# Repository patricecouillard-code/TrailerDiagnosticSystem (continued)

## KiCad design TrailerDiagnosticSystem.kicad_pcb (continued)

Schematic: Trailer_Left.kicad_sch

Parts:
D1601: MUR1520G; TO-220-2_Vertical
D1602: P6KE39A; D_DO-15_P10.16mm_Horizontal_Zener
DZ1601: 1N5242B; D_DO-35_SOD27_P7.62mm_Horizontal_Zener
F1601: MF-R700; PTC_Bourns_MF-R_P10.20mm_W24.2mm
Q1601: 2N7000; TO-92_Inline_Wide_SGD
Q1602: IRF4905PBF; TO-220-3_Vertical
Q1603: 2N3906; TO-92_Inline_Wide_EBC
R1601, R1603, R1605, R1607: 10kΩ; R_Axial_DIN0207_L6.3mm_D2.5mm_P10.16mm_Horizontal
R1602, R1606: 1kΩ; R_Axial_DIN0207_L6.3mm_D2.5mm_P10.16mm_Horizontal
R1604: 2.7kΩ; R_Axial_DIN0207_L6.3mm_D2.5mm_P10.16mm_Horizontal
R1608: 39kΩ; R_Axial_DIN0207_L6.3mm_D2.5mm_P10.16mm_Horizontal
R1609: 12Ω 2W; R_Axial_DIN0414_L11.9mm_D4.5mm_P15.24mm_Horizontal; MPN PR02000201209JR500
R1610, R1611: 10kΩ; TRIM_3296W1103LF; MPN 3296W-1-103LF
R1612, R1613: 4.7kΩ; R_Axial_DIN0207_L6.3mm_D2.5mm_P10.16mm_Horizontal
SW1601: 82-4153.2000
U1601: LM2901N; DIP-14_W7.62mm_Socket

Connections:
/Canal_Left/Bloc_Test_Left/Trailer_Court_Left: R1613.1, U1601.13; also elsewhere on the board
/Canal_Left/Bloc_Test_Left/Trailer_Ouvert_Left: R1612.1, U1601.1; also elsewhere on the board
/Canal_Left/Trailer_Left/Court_Sense: R1605.1, R1608.1, U1601.10 (-)
/Canal_Left/Trailer_Left/I_Present: R1604.1, R1607.2, U1601.6 (-)
/Trailer_Fil_Left: D1601.1 (K), D1602.1 (K), R1606.1, R1608.2, R1609.2; also elsewhere on the board
Facade_Btn_Left: Q1601.2 (G), R1601.2, SW1601.2 (B); also elsewhere on the board
GND: D1602.2 (A), Q1601.1 (S), R1601.1, R1604.2, R1605.2, R1610.3, R1611.1, SW1601.3 (C), U1601.5 (+), U1601.9 (+), U1601.12 (V-); also elsewhere on the board
unnamed: D1601.2 (A), Q1602.2 (D), Q1603.1 (E), R1609.1
unnamed: DZ1601.2 (A), Q1602.1 (G), R1602.2, R1603.1
unnamed: DZ1601.1 (K), F1601.2, Q1602.3 (S), R1603.2
unnamed: Q1601.3 (D), R1602.1
unnamed: Q1603.2 (B), R1606.2
unnamed: Q1603.3 (C), R1607.1
unnamed: R1610.2, U1601.7 (+)
unnamed: R1611.2, U1601.11 (+)
Trailer_V_Arm: F1601.1; also elsewhere on the board
V_Ref: R1610.1, R1611.3, R1612.2, R1613.2, SW1601.1 (A), U1601.3 (V+), U1601.4 (-), U1601.8 (-); also elsewhere on the board

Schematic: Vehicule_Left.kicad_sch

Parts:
OC1501, OC1502: PC817; DIP-4_W7.62mm_LongPads
Q1501: IRLZ44N; TO-220-3_Vertical_GDS
R1501: 12Ω 25W; TerminalBlock_Phoenix_PT-1,5-2-3.5-H_1x02_P3.50mm_Horizontal; MPN HSA2512RJ
R1502: 0.2Ω 5W; R_Axial_Power_L25.0mm_W9.0mm_P27.94mm; MPN SQP500JB-0R2
R1503, R1504, R1505: 4.7kΩ; R_Axial_DIN0207_L6.3mm_D2.5mm_P10.16mm_Horizontal
R1506, R1507: 1kΩ; R_Axial_DIN0207_L6.3mm_D2.5mm_P10.16mm_Horizontal
R1508: 100kΩ; R_Axial_DIN0207_L6.3mm_D2.5mm_P10.16mm_Horizontal
R1509: 10kΩ; R_Axial_DIN0207_L6.3mm_D2.5mm_P10.16mm_Horizontal
R1510, R1511, R1512: 10kΩ; TRIM_3296W1103LF; MPN 3296W-1-103LF
U1501: LM2901N; DIP-14_W7.62mm_Socket

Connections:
/Canal_Left/Bloc_Test_Left/Vehic_Court_Left: OC1501.4; also elsewhere on the board
/Canal_Left/Bloc_Test_Left/Vehic_Ouvert_Left: OC1502.4; also elsewhere on the board
/Canal_Left/Vehicule_Left/Injection_Drain: Q1501.2 (D), R1501.2
/Canal_Left/Vehicule_Left/Injection_Fault: Q1501.1 (G), R1503.1, U1501.2
/Canal_Left/Vehicule_Left/Opto_Court: OC1501.2, R1505.1, U1501.13
/Canal_Left/Vehicule_Left/Opto_Ouvert: OC1502.2, R1504.1, U1501.1
/Canal_Left/Vehicule_Left/Seuil_Court: R1512.2, U1501.10 (-)
/Canal_Left/Vehicule_Left/Seuil_Injection: R1510.2, U1501.4 (-)
/Canal_Left/Vehicule_Left/Seuil_Ouvert: R1511.2, U1501.7 (+)
/Canal_Left/Vehicule_Left/Vehic_Shunt_Haut: Q1501.3 (S), R1502.1, U1501.6 (-), U1501.11 (+)
/Vehic_Fil_Left: R1501.1, R1508.1; also elsewhere on the board
GND: OC1501.3, OC1502.3, R1502.2, R1509.2, R1510.3, R1511.3, R1512.3, U1501.9 (+), U1501.12 (V-); also elsewhere on the board
unnamed: OC1501.1, R1506.2
unnamed: OC1502.1, R1507.2
unnamed: R1508.2, R1509.1, U1501.5 (+)
V_Ref: R1503.2, R1504.2, R1505.2, R1506.1, R1507.1, R1510.1, R1511.1, R1512.1, U1501.3 (V+), U1501.8 (-); also elsewhere on the board

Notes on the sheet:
Injection
Ouvvert
Non_Utilisé
Court-circuit

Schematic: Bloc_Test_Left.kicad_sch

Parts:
D1701, D1702, D1703, D1704, D1705, D1706, D1707, D1708, D1709, D1710, D1711, D1712, D1713, D1714, D1715, D1716, D1717, D1718, D1719, D1720, D1721, D1722, D1723: 1N4148; D_DO-35_SOD27_P7.62mm_Horizontal
D1724: RGB 5mm CA; LED_D5.0mm-4_RGB_Staggered_Pins; MPN WP154A4SEJ3VBDZGW/CA
Q1701, Q1702, Q1703, Q1704, Q1705, Q1706: 2N7000; TO-92_Inline_Wide_SGD
R1701, R1704, R1707, R1708, R1710, R1711, R1715: 4.7kΩ; R_Axial_DIN0207_L6.3mm_D2.5mm_P10.16mm_Horizontal
R1702, R1705, R1709: 470kΩ; R_Axial_DIN0207_L6.3mm_D2.5mm_P10.16mm_Horizontal
R1703, R1706: 100kΩ; R_Axial_DIN0207_L6.3mm_D2.5mm_P10.16mm_Horizontal
R1712: 680Ω; R_Axial_DIN0207_L6.3mm_D2.5mm_P10.16mm_Horizontal
R1713: 470Ω; R_Axial_DIN0207_L6.3mm_D2.5mm_P10.16mm_Horizontal
R1714: 150Ω; R_Axial_DIN0207_L6.3mm_D2.5mm_P10.16mm_Horizontal

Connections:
/Canal_Left/Bloc_Test_Left/Bleu: D1704.2 (A), D1713.2 (A), D1722.2 (A), D1723.2 (A), R1715.1
/Canal_Left/Bloc_Test_Left/Court: D1709.1 (K), D1710.1 (K), D1711.2 (A), D1717.2 (A), Q1701.2 (G), R1706.2
/Canal_Left/Bloc_Test_Left/Fault_Actif: D1711.1 (K), D1712.1 (K), D1713.1 (K), Q1702.2 (G), R1705.1
/Canal_Left/Bloc_Test_Left/Not_Btn: D1723.1 (K), Q1703.3 (D), R1711.2
/Canal_Left/Bloc_Test_Left/Ouvert: D1703.2 (A), D1705.1 (K), D1706.1 (K), D1712.2 (A), D1718.2 (A), R1703.2
/Canal_Left/Bloc_Test_Left/Ouvert_Ou_Bleu: D1703.1 (K), D1704.1 (K), Q1701.3 (D), Q1706.2 (G), R1702.2
/Canal_Left/Bloc_Test_Left/Rouge_Enable: D1717.1 (K), D1718.1 (K), Q1704.2 (G), R1709.2
/Canal_Left/Bloc_Test_Left/Trailer_Court_Actif: D1707.2 (A), D1708.2 (A), D1710.2 (A), D1716.2 (A), R1704.1
/Canal_Left/Bloc_Test_Left/Trailer_Court_Left: D1707.1 (K); also elsewhere on the board
/Canal_Left/Bloc_Test_Left/Trailer_Ouvert_Actif: D1706.2 (A), D1719.2 (A), D1720.2 (A), D1721.2 (A), R1710.1
/Canal_Left/Bloc_Test_Left/Trailer_Ouvert_Left: D1719.1 (K); also elsewhere on the board
/Canal_Left/Bloc_Test_Left/Vehic_Court_Actif: D1701.2 (A), D1702.2 (A), D1709.2 (A), R1701.1
/Canal_Left/Bloc_Test_Left/Vehic_Court_Left: D1701.1 (K); also elsewhere on the board
/Canal_Left/Bloc_Test_Left/Vehic_Ouvert_Actif: D1705.2 (A), D1714.2 (A), D1715.2 (A), R1708.1
/Canal_Left/Bloc_Test_Left/Vehic_Ouvert_Left: D1714.1 (K); also elsewhere on the board
/Canal_Left/Bloc_Test_Left/Vert_Enable: Q1702.3 (D), Q1705.2 (G), R1707.2
Facade_Btn_Left: D1716.1 (K), D1721.1 (K), Q1703.2 (G); also elsewhere on the board
Facade_Left_B: D1724.3 (BK), R1714.2; also elsewhere on the board
Facade_Left_G: D1724.4 (GK), R1713.2; also elsewhere on the board
Facade_Left_R: D1724.1 (RK), R1712.2; also elsewhere on the board
GND: Q1701.1 (S), Q1702.1 (S), Q1703.1 (S), Q1704.1 (S), Q1705.1 (S), Q1706.1 (S), R1702.1, R1703.1, R1705.2, R1706.1, R1709.1; also elsewhere on the board
Mode_Trailer: D1708.1 (K), D1720.1 (K), D1722.1 (K); also elsewhere on the board
Mode_Vehic: D1702.1 (K), D1715.1 (K); also elsewhere on the board
unnamed: Q1704.3 (D), R1712.1
unnamed: Q1705.3 (D), R1713.1
unnamed: Q1706.3 (D), R1714.1
V_Ref: D1724.2 (A), R1701.2, R1704.2, R1707.1, R1708.2, R1710.2, R1711.1, R1715.2; also elsewhere on the board

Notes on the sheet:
====================================== NIVEAU 3 ==================
3ième Porte "ET" (Ouvert_V_Actif_Left)
Porte OU Fault_Actif_Left (3 entrées) + inverseur vert
5ième Porte "ET" (Bleu_Left)
Porte OU Rouge_Enable_Left
Porte OU Ouvert_Ou_Bleu_Left + override
2ième Porte "ET" (Court_T_Actif_Left)
========================================================================== NIVEAU 1 ==========================================================================
Inverseur (Dépendance de Bleu_Left)
=========================================== NIVEAU 2 =================================================
1ère Porte "ET" (Court_V_Actif_Left)
2ième Porte "OU" (Court_Left)
4ième Porte "ET" (Ouvert_T_Actif_Left)
1ère Porte "OU" (Ouvert_Left)

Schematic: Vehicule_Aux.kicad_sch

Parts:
C2701: 4.7µF 63V; C_Rect_L19.0mm_W7.0mm_P15.00mm_MKS4; MPN MKS4C044704D00KSSD 10%
D2701: RGB 5mm CA (ambre); LED_D5.0mm-4_RGB_Staggered_Pins; MPN WP154A4SEJ3VBDZGW/CA
OC2701, OC2702: PC817; DIP-4_W7.62mm_LongPads
Q2701: IRLZ44N; TO-220-3_Vertical_GDS
Q2702, Q2703: 2N7000; TO-92_Inline_Wide_SGD
R2701: 0.05Ω 5W; R_Axial_Power_L25.0mm_W9.0mm_P27.94mm; MPN 15FR050E
R2702, R2716: 100kΩ; R_Axial_DIN0207_L6.3mm_D2.5mm_P10.16mm_Horizontal
R2703, R2704, R2705: 10kΩ; R_Axial_DIN0207_L6.3mm_D2.5mm_P10.16mm_Horizontal
R2706, R2708: 4.7kΩ; R_Axial_DIN0207_L6.3mm_D2.5mm_P10.16mm_Horizontal
R2707: 330kΩ; R_Axial_DIN0207_L6.3mm_D2.5mm_P10.16mm_Horizontal
R2709: 4.7Ω 50W; TerminalBlock_Phoenix_PT-1,5-2-3.5-H_1x02_P3.50mm_Horizontal; MPN HSA504R7J
R2710, R2711: 1kΩ; R_Axial_DIN0207_L6.3mm_D2.5mm_P10.16mm_Horizontal
R2712, R2713, R2714: 10kΩ; TRIM_3296W1103LF; MPN 3296W-1-103LF
R2715: 100Ω; R_Axial_DIN0207_L6.3mm_D2.5mm_P10.16mm_Horizontal
TH2701: Thermostat 95°C NC; TerminalBlock_Phoenix_PT-1,5-2-3.5-H_1x02_P3.50mm_Horizontal; MPN CS709525Y
U2701: LM2901N; DIP-14_W7.62mm_Socket

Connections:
/Canal_Aux/Bloc_Test_Aux/Vehic_Court_Aux: OC2702.4; also elsewhere on the board
/Canal_Aux/Bloc_Test_Aux/Vehic_Ouvert_Aux: OC2701.4; also elsewhere on the board
/Canal_Aux/Vehicule_Aux/Etire: C2701.1, R2707.1, U2701.1, U2701.9 (+)
/Canal_Aux/Vehicule_Aux/Injection_Fault: Q2701.1 (G), Q2703.3 (D), R2706.1, U2701.2
/Canal_Aux/Vehicule_Aux/Opto_Ouvert: OC2701.2, U2701.14
/Canal_Aux/Vehicule_Aux/Seuil_Court: R2714.2, U2701.10 (-)
/Canal_Aux/Vehicule_Aux/Seuil_Injection: R2712.2, U2701.4 (-)
/Canal_Aux/Vehicule_Aux/Seuil_Ouvert: R2713.2, U2701.7 (+)
/Vehic_Fil_Aux: R2702.1, R2709.1; also elsewhere on the board
Facade_DEL_Surchauffe_Aux: D2701.1 (K), R2715.2; also elsewhere on the board
GND: C2701.2, OC2701.3, OC2702.3, Q2702.1 (S), Q2703.1 (S), R2701.2, R2704.2, R2705.2, R2712.3, R2713.3, R2714.3, TH2701.2, U2701.12 (V-); also elsewhere on the board
unnamed: OC2701.1, R2710.2
unnamed: OC2702.1, R2711.2
unnamed: OC2702.2, R2708.1, U2701.13
unnamed: Q2701.2 (D), R2709.2
unnamed: Q2701.3 (S), R2701.1, U2701.6 (-), U2701.11 (+)
unnamed: Q2702.3 (D), R2715.1
unnamed: Q2702.2 (G), Q2703.2 (G), R2716.2, TH2701.1
unnamed: R2702.2, R2704.1, U2701.5 (+)
unnamed: R2703.2, R2705.1, U2701.8 (-)
V_Ref: D2701.2 (A), R2703.1, R2706.2, R2707.2, R2708.2, R2710.1, R2711.1, R2712.1, R2713.1, R2714.1, R2716.1, U2701.3 (V+); also elsewhere on the board

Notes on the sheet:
Protection contre surchauffe
Module du voltmetre/ampèremetre

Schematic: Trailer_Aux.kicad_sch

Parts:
D2801: P6KE39A; D_DO-15_P10.16mm_Horizontal_Zener
DZ2801: 1N5242B; D_DO-35_SOD27_P7.62mm_Horizontal_Zener
F2801: MF-R160; PTC_Bourns_MF-R_P5.10mm_W12.0mm
Q2801: 2N7000; TO-92_Inline_Wide_SGD
Q2802: IRF4905PBF; TO-220-3_Vertical
R2801, R2803, R2806: 10kΩ; R_Axial_DIN0207_L6.3mm_D2.5mm_P10.16mm_Horizontal
R2802: 1kΩ; R_Axial_DIN0207_L6.3mm_D2.5mm_P10.16mm_Horizontal
R2804: 12Ω 50W; TerminalBlock_Phoenix_PT-1,5-2-3.5-H_1x02_P3.50mm_Horizontal; MPN HSA5012RJ
R2805: 39kΩ; R_Axial_DIN0207_L6.3mm_D2.5mm_P10.16mm_Horizontal
R2807, R2808: 10kΩ; TRIM_3296W1103LF; MPN 3296W-1-103LF
R2809: 100kΩ; R_Axial_DIN0207_L6.3mm_D2.5mm_P10.16mm_Horizontal
R2810, R2811: 4.7kΩ; R_Axial_DIN0207_L6.3mm_D2.5mm_P10.16mm_Horizontal
SW2801: 82-4153.2000
TH2801: Thermostat 95°C NC; TerminalBlock_Phoenix_PT-1,5-2-3.5-H_1x02_P3.50mm_Horizontal; MPN CS709525Y
U2801: LM2901N; DIP-14_W7.62mm_Socket

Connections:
/Canal_Aux/Bloc_Test_Aux/Trailer_Court_Aux: R2811.1, U2801.13; also elsewhere on the board
/Canal_Aux/Bloc_Test_Aux/Trailer_Ouvert_Aux: R2810.1, U2801.1; also elsewhere on the board
/Canal_Aux/Trailer_Aux/Trailer_Mesure: R2805.2, R2806.2, U2801.7 (+), U2801.10 (-)
/Trailer_Fil_Aux: D2801.1 (K), R2804.1, R2805.1; also elsewhere on the board
Facade_Btn_Aux: Q2801.2 (G), R2801.1, SW2801.2 (B); also elsewhere on the board
GND: D2801.2 (A), Q2801.1 (S), R2801.2, R2806.1, R2807.3, R2808.3, SW2801.3 (C), U2801.5 (+), U2801.9 (+), U2801.12 (V-); also elsewhere on the board
unnamed: DZ2801.2 (A), Q2802.1 (G), R2802.1, R2803.1
unnamed: DZ2801.1 (K), F2801.2, Q2802.3 (S), R2803.2
unnamed: Q2801.3 (D), R2802.2
unnamed: Q2802.2 (D), TH2801.1
unnamed: R2804.2, TH2801.2
unnamed: R2808.1, R2809.1
unnamed: R2807.2, U2801.6 (-)
unnamed: R2808.2, U2801.11 (+)
Trailer_V_Arm: F2801.1; also elsewhere on the board
V_Ref: R2807.1, R2809.2, R2810.2, R2811.2, SW2801.1 (A), U2801.3 (V+), U2801.4 (-), U2801.8 (-); also elsewhere on the board

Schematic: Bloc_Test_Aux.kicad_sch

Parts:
D2901, D2902, D2903, D2904, D2905, D2906, D2907, D2908, D2909, D2910, D2911, D2912, D2913, D2914, D2915, D2916, D2917, D2918, D2919, D2920, D2921, D2922, D2923: 1N4148; D_DO-35_SOD27_P7.62mm_Horizontal
D2924: RGB 5mm CA; LED_D5.0mm-4_RGB_Staggered_Pins; MPN WP154A4SEJ3VBDZGW/CA
Q2901, Q2902, Q2903, Q2904, Q2905, Q2906: 2N7000; TO-92_Inline_Wide_SGD
R2901, R2904, R2907, R2908, R2910, R2911, R2912: 4.7kΩ; R_Axial_DIN0207_L6.3mm_D2.5mm_P10.16mm_Horizontal
R2902, R2905, R2909: 470kΩ; R_Axial_DIN0207_L6.3mm_D2.5mm_P10.16mm_Horizontal
R2903, R2906: 100kΩ; R_Axial_DIN0207_L6.3mm_D2.5mm_P10.16mm_Horizontal
R2913: 680Ω; R_Axial_DIN0207_L6.3mm_D2.5mm_P10.16mm_Horizontal
R2914: 470Ω; R_Axial_DIN0207_L6.3mm_D2.5mm_P10.16mm_Horizontal
R2915: 150Ω; R_Axial_DIN0207_L6.3mm_D2.5mm_P10.16mm_Horizontal

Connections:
/Canal_Aux/Bloc_Test_Aux/Bleu: D2904.2 (A), D2913.2 (A), D2922.2 (A), D2923.2 (A), R2912.1
/Canal_Aux/Bloc_Test_Aux/Court: D2909.1 (K), D2910.1 (K), D2911.2 (A), D2917.2 (A), Q2901.2 (G), R2906.2
/Canal_Aux/Bloc_Test_Aux/Fault_Actif: D2911.1 (K), D2912.1 (K), D2913.1 (K), Q2902.2 (G), R2905.1
/Canal_Aux/Bloc_Test_Aux/Not_Btn: D2923.1 (K), Q2903.3 (D), R2911.2
/Canal_Aux/Bloc_Test_Aux/Ouvert: D2903.2 (A), D2905.1 (K), D2906.1 (K), D2912.2 (A), D2918.2 (A), R2903.2
/Canal_Aux/Bloc_Test_Aux/Ouvert_Ou_Bleu: D2903.1 (K), D2904.1 (K), Q2901.3 (D), Q2906.2 (G), R2902.2
/Canal_Aux/Bloc_Test_Aux/Rouge_Enable: D2917.1 (K), D2918.1 (K), Q2904.2 (G), R2909.2
/Canal_Aux/Bloc_Test_Aux/Trailer_Court_Actif: D2907.2 (A), D2908.2 (A), D2910.2 (A), D2916.2 (A), R2904.1
/Canal_Aux/Bloc_Test_Aux/Trailer_Court_Aux: D2907.1 (K); also elsewhere on the board
/Canal_Aux/Bloc_Test_Aux/Trailer_Ouvert_Actif: D2906.2 (A), D2919.2 (A), D2920.2 (A), D2921.2 (A), R2910.1
/Canal_Aux/Bloc_Test_Aux/Trailer_Ouvert_Aux: D2919.1 (K); also elsewhere on the board
/Canal_Aux/Bloc_Test_Aux/Vehic_Court_Actif: D2901.2 (A), D2902.2 (A), D2909.2 (A), R2901.1
/Canal_Aux/Bloc_Test_Aux/Vehic_Court_Aux: D2901.1 (K); also elsewhere on the board
/Canal_Aux/Bloc_Test_Aux/Vehic_Ouvert_Actif: D2905.2 (A), D2914.2 (A), D2915.2 (A), R2908.1
/Canal_Aux/Bloc_Test_Aux/Vehic_Ouvert_Aux: D2914.1 (K); also elsewhere on the board
/Canal_Aux/Bloc_Test_Aux/Vert_Enable: Q2902.3 (D), Q2905.2 (G), R2907.2
Facade_Aux_B: D2924.3 (BK), R2915.2; also elsewhere on the board
Facade_Aux_G: D2924.4 (GK), R2914.2; also elsewhere on the board
Facade_Aux_R: D2924.1 (RK), R2913.2; also elsewhere on the board
Facade_Btn_Aux: D2916.1 (K), D2921.1 (K), Q2903.2 (G); also elsewhere on the board
GND: Q2901.1 (S), Q2902.1 (S), Q2903.1 (S), Q2904.1 (S), Q2905.1 (S), Q2906.1 (S), R2902.1, R2903.1, R2905.2, R2906.1, R2909.1; also elsewhere on the board
Mode_Trailer: D2908.1 (K), D2920.1 (K), D2922.1 (K); also elsewhere on the board
Mode_Vehic: D2902.1 (K), D2915.1 (K); also elsewhere on the board
unnamed: Q2904.3 (D), R2913.1
unnamed: Q2905.3 (D), R2914.1
unnamed: Q2906.3 (D), R2915.1
V_Ref: D2924.2 (A), R2901.2, R2904.2, R2907.1, R2908.2, R2910.2, R2911.1, R2912.2; also elsewhere on the board

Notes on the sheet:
1ère Porte "ET" (Court_V_Actif_Aux)
========================================================================== NIVEAU 1 ==========================================================================
Porte OU Rouge_Enable_Aux
Inverseur (Dépendance de Bleu_Aux)
4ième Porte "ET" (Ouvert_T_Actif_Aux)
====================================== NIVEAU 3 ==================
1ère Porte "OU" (Ouvert_Aux)
Porte OU Ouvert_Ou_Bleu_Aux + override
5ième Porte "ET" (Bleu_Aux)
2ième Porte "OU" (Court_Aux)
3ième Porte "ET" (Ouvert_V_Actif_Aux)
Porte OU Fault_Actif_Aux (3 entrées) + inverseur vert
2ième Porte "ET" (Court_T_Actif_Aux)
=========================================== NIVEAU 2 =================================================

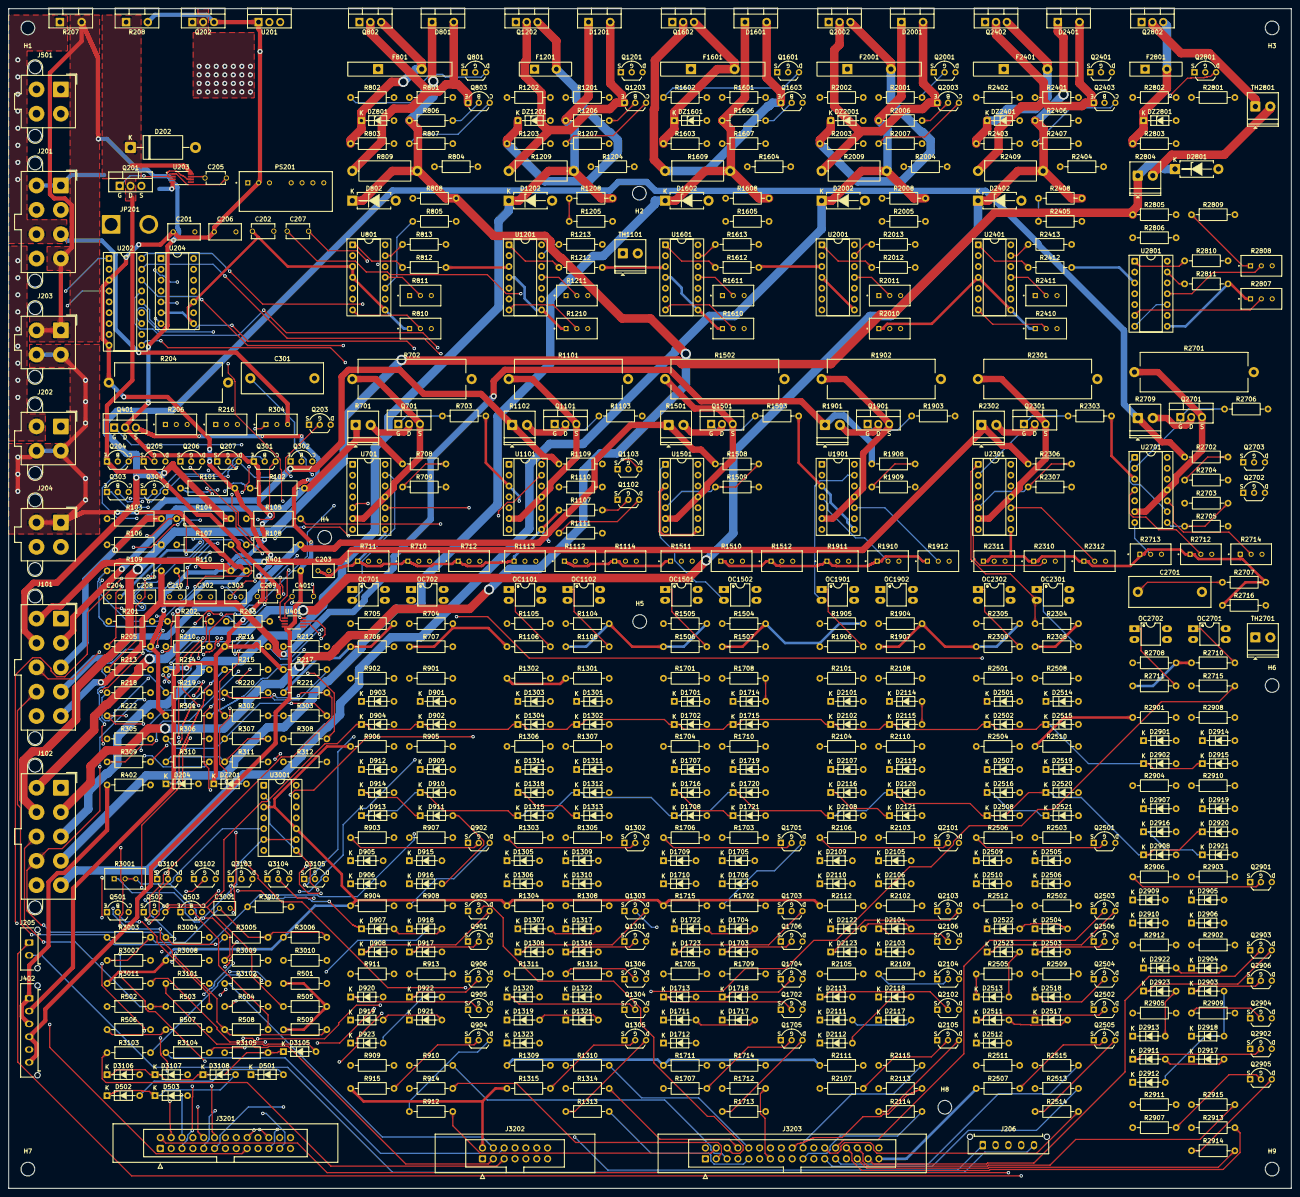
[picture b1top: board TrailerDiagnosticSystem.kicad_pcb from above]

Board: 4 copper layers, 300.3 x 276.2 mm, 641 parts (0 on the bottom side), 383 nets.

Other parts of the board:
H1, H2, H3, H4, H5, H6, H7, H8, H9: M3; MountingHole_3.2mm_M3

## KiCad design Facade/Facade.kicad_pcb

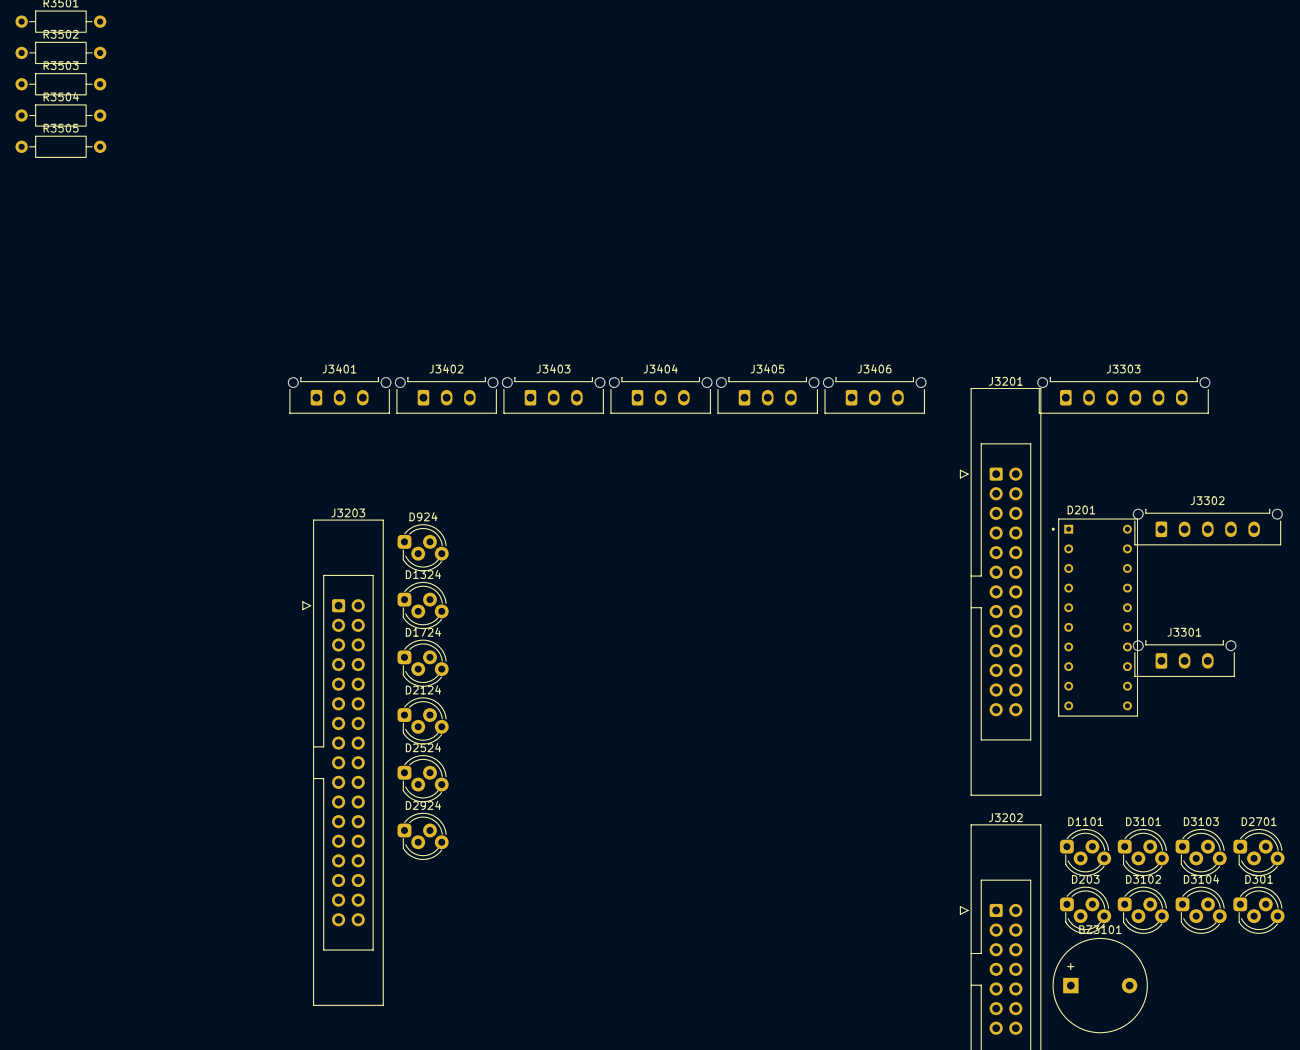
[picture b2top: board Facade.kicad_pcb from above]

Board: 2 copper layers, 33 parts (0 on the bottom side), 65 nets, no tracks yet.

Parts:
BZ3101: Buzzer 5V; Buzzer_12x9.5RM7.6
D201: OSX10201-GYR1; DIP760W45P254L2550H815Q20B
D203, D3101, D3102, D3103, D3104: RGB 5mm CA (rouge); LED_D5.0mm-4_RGB_Staggered_Pins
D301, D1101, D2701: RGB 5mm CA (ambre); LED_D5.0mm-4_RGB_Staggered_Pins
D924, D1324, D1724, D2124, D2524, D2924: RGB 5mm CA; LED_D5.0mm-4_RGB_Staggered_Pins
J3201: IDC 2x13; IDC-Header_2x13_P2.54mm_Latch_Vertical
J3202: IDC 2x07; IDC-Header_2x07_P2.54mm_Latch_Vertical
J3203: IDC 2x17; IDC-Header_2x17_P2.54mm_Latch_Vertical
J3301, J3401, J3402, J3403, J3404, J3405, J3406: Micro-Fit 3.0 1x03; Molex_Micro-Fit_3.0_43650-0315_1x03_P3.00mm_Vertical
J3302: Micro-Fit 3.0 1x05; Molex_Micro-Fit_3.0_43650-0515_1x05_P3.00mm_Vertical
J3303: Micro-Fit 3.0 1x06; Molex_Micro-Fit_3.0_43650-0615_1x06_P3.00mm_Vertical
R3501, R3503: 820Ω; R_Axial_DIN0207_L6.3mm_D2.5mm_P10.16mm_Horizontal
R3502, R3504: 1.2kΩ; R_Axial_DIN0207_L6.3mm_D2.5mm_P10.16mm_Horizontal
R3505: 270Ω; R_Axial_DIN0207_L6.3mm_D2.5mm_P10.16mm_Horizontal

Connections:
/Bottom_Zone/Batt_Ext_Rouge: D301.1 (RK), R3505.1
/Bottom_Zone/Facade_Buzzer: BZ3101.2 (-), J3202.9
/Bottom_Zone/Facade_DEL_Batt_Ext: D301.2 (A), J3202.13
/Bottom_Zone/Facade_DEL_Court_Bus: D3102.1 (RK), J3202.4
/Bottom_Zone/Facade_DEL_Incoherence: D3103.1 (RK), J3202.5
/Bottom_Zone/Facade_DEL_Inversion: D203.1 (RK), J3202.7
/Bottom_Zone/Facade_DEL_Masse: D3104.1 (RK), J3202.6
/Bottom_Zone/Facade_DEL_Surchauffe_Aux: J3202.12, R3503.2, R3504.2
/Bottom_Zone/Facade_DEL_Surchauffe_Brake: J3202.11, R3501.2, R3502.2
/Bottom_Zone/Facade_DEL_Surtension: D3101.1 (RK), J3202.3
/Bottom_Zone/Surchauffe_Aux_Rouge: D2701.1 (RK), R3503.1
/Bottom_Zone/Surchauffe_Aux_Vert: D2701.4 (GK), R3504.1
/Bottom_Zone/Surchauffe_Brake_Rouge: D1101.1 (RK), R3501.1
/Bottom_Zone/Surchauffe_Brake_Vert: D1101.4 (GK), R3502.1
/Bottom_Zone/V_Ref: BZ3101.1 (+), D1101.2 (A), D2701.2 (A), D3101.2 (A), D3102.2 (A), D3103.2 (A), D3104.2 (A), J3202.2
/Center_Zone/Facade_Aux_B: D2924.3 (BK), J3203.30
/Center_Zone/Facade_Aux_G: D2924.4 (GK), J3203.29
/Center_Zone/Facade_Aux_R: D2924.1 (RK), J3203.28
/Center_Zone/Facade_Backup_B: D2524.3 (BK), J3203.25
/Center_Zone/Facade_Backup_G: D2524.4 (GK), J3203.24
/Center_Zone/Facade_Backup_R: D2524.1 (RK), J3203.23
/Center_Zone/Facade_Brake_B: D1324.3 (BK), J3203.10
/Center_Zone/Facade_Brake_G: D1324.4 (GK), J3203.9
/Center_Zone/Facade_Brake_R: D1324.1 (RK), J3203.8
/Center_Zone/Facade_Btn_Aux: J3203.31, J3406.2
/Center_Zone/Facade_Btn_Backup: J3203.26, J3405.2
/Center_Zone/Facade_Btn_Brake: J3203.11, J3402.2
/Center_Zone/Facade_Btn_Left: J3203.16, J3403.2
/Center_Zone/Facade_Btn_Right: J3203.21, J3404.2
/Center_Zone/Facade_Btn_Tail: J3203.6, J3401.2
/Center_Zone/Facade_Left_B: D1724.3 (BK), J3203.15
/Center_Zone/Facade_Left_G: D1724.4 (GK), J3203.14
/Center_Zone/Facade_Left_R: D1724.1 (RK), J3203.13
/Center_Zone/Facade_Right_B: D2124.3 (BK), J3203.20
/Center_Zone/Facade_Right_G: D2124.4 (GK), J3203.19
/Center_Zone/Facade_Right_R: D2124.1 (RK), J3203.18
/Center_Zone/Facade_Tail_B: D924.3 (BK), J3203.5
/Center_Zone/Facade_Tail_G: D924.4 (GK), J3203.4
/Center_Zone/Facade_Tail_R: D924.1 (RK), J3203.3
/Center_Zone/V_Ref: D924.2 (A), D1324.2 (A), D1724.2 (A), D2124.2 (A), D2524.2 (A), D2924.2 (A), J3203.2, J3203.33, J3401.1, J3402.1, J3403.1, J3404.1, J3405.1, J3406.1
/Top_Zone/Facade_Jauge_1: D201.11, J3201.17
/Top_Zone/Facade_Jauge_2: D201.12, J3201.18
/Top_Zone/Facade_Jauge_3: D201.13, J3201.19
/Top_Zone/Facade_Jauge_4: D201.14, J3201.20
/Top_Zone/Facade_Jauge_5: D201.15, J3201.21
/Top_Zone/Facade_Jauge_6: D201.16, J3201.22
/Top_Zone/Facade_Jauge_7: D201.17, J3201.23
/Top_Zone/Facade_Jauge_8: D201.18, J3201.24
/Top_Zone/Facade_Jauge_9: D201.19, J3201.25
/Top_Zone/Facade_Jauge_10: D201.20, J3201.26
/Top_Zone/Facade_VLed_Jauge: D201.1, D201.2, D201.3, D201.4, D201.5, D201.6, D201.7, D201.8, D201.9, D201.10, J3201.16
/Top_Zone/Facade_VM_Mesure: J3201.2, J3302.5
/Top_Zone/Facade_VM_Sel_Batt: J3201.4, J3303.1
/Top_Zone/Facade_VM_Sel_Trailer_Aux: J3201.12, J3302.3
/Top_Zone/Facade_VM_Sel_Trailer_Pince: J3201.13, J3302.4
/Top_Zone/Facade_VM_Sel_Vehic_Aux: J3201.10, J3302.1
/Top_Zone/Facade_VM_Sel_Vehic_Backup: J3201.9, J3303.6
/Top_Zone/Facade_VM_Sel_Vehic_Brake: J3201.6, J3303.3
/Top_Zone/Facade_VM_Sel_Vehic_Left: J3201.7, J3303.4
/Top_Zone/Facade_VM_Sel_Vehic_Pince: J3201.11, J3302.2
/Top_Zone/Facade_VM_Sel_Vehic_Right: J3201.8, J3303.5
/Top_Zone/Facade_VM_Sel_Vehic_Tail: J3201.5, J3303.2
/Top_Zone/Mode_Trailer: J3201.14, J3301.2
/Top_Zone/V_Ref: J3201.15, J3301.3
GND: D203.2 (A), D301.4 (GK), J3201.1, J3201.3, J3202.1, J3202.8, J3202.10, J3202.14, J3203.1, J3203.7, J3203.12, J3203.17, J3203.22, J3203.27, J3203.32, J3203.34, J3301.1, J3401.3, J3402.3, J3403.3, J3404.3, J3405.3, J3406.3, R3505.2
